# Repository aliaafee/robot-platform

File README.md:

# Robot Platform

An arduino based wheeled robot platform.

18650 battery holder

protection circuite
holder for two

2S 20A 7.4V w/Balance Lithium Li-ion 18650 Battery BMS Pack Protection PCB Board

LM2596 DC-DC Buck Converter Step Down Adjustable Power Supply Module

B0505S circuit isolator DC-DC converter

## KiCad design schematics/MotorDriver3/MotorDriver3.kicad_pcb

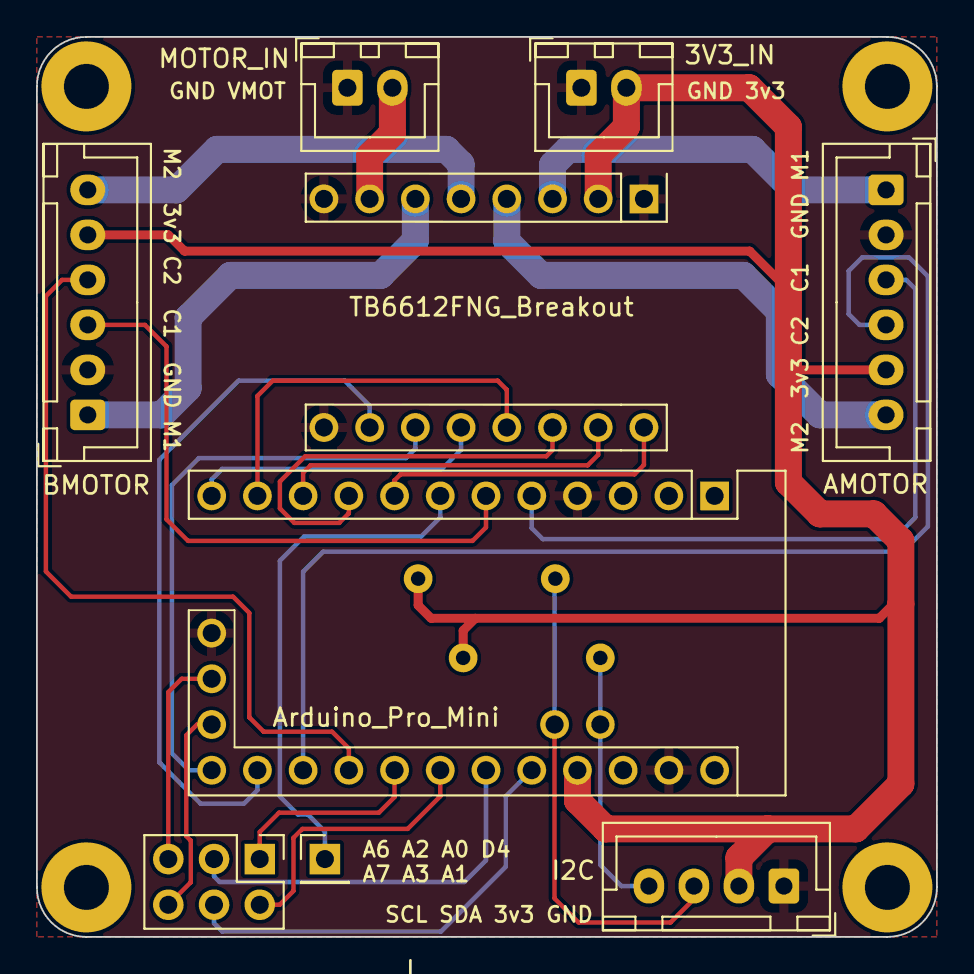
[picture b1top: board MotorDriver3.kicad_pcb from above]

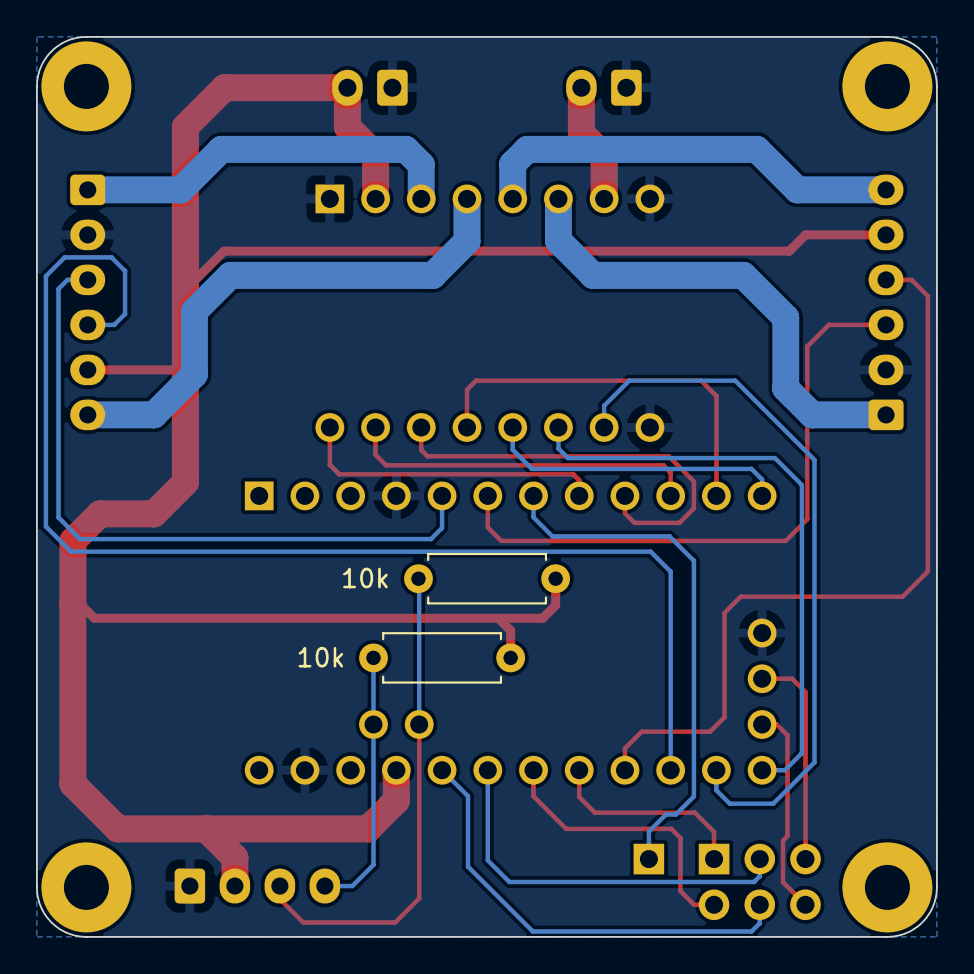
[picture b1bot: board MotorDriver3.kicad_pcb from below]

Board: 2 copper layers, 50.0 x 50.0 mm, 15 parts (2 on the bottom side), 27 nets.

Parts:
A2: Arduino_Pro_Mini; Arduino Pro Mini
H1, H2, H3, H4: MountingHole_Pad; MountingHole_2.5mm_Pad
J1: AMOTOR; JST_XH_B6B-XH-A_1x06_P2.50mm_Vertical
J2: BMOTOR; JST_XH_B6B-XH-A_1x06_P2.50mm_Vertical
J3: I2C; JST_XH_B4B-XH-A_1x04_P2.50mm_Vertical
J4: AnalogPins; PinHeader_2x03_P2.54mm_Vertical
J5: MOTOR_IN; JST_XH_B2B-XH-A_1x02_P2.50mm_Vertical
J6: 3V3_IN; JST_XH_B2B-XH-A_1x02_P2.50mm_Vertical
J7: Digital Pins; PinHeader_1x01_P2.54mm_Vertical
R1, R2: 10k; R_Axial_DIN0207_L6.3mm_D2.5mm_P7.62mm_Horizontal
U1: TB6612FNG_Breakout; TB6612FBG_Breakout

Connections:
+3V3: A2.26 (VCC), J1.5, J2.5, J3.2, J6.2, R1.1, R2.1, U1.2 (VCC)
A0: A2.20 (A0), J4.1
A1: A2.21 (A1), J4.2
A2: A2.22 (A2), J4.3
A3: A2.23 (A3), J4.4
A6: A2.14 (A6), J4.5
A7: A2.15 (A7), J4.6
AIN1: A2.10 (D7), U1.15 (AIN2)
AIN2: A2.9 (D6), U1.14 (AIN1)
AINT1: A2.5 (D2), J1.3
AINT2: A2.18 (D12), J1.4
AO1: J1.1, U1.3 (AO1)
AO2: J1.6, U1.4 (AO2)
BIN1: A2.12 (D9), U1.12 (BIN1)
BIN2: A2.16 (D10), U1.11 (BIN2)
BINT1: A2.6 (D3), J2.3
BINT2: A2.19 (D13), J2.4
BO1: J2.1, U1.6 (BO1)
BO2: J2.6, U1.5 (BO2)
D4: A2.7 (D4), J7.1
GND: A2.4 (GND), A2.13 (GND), A2.28 (GND), J1.2, J2.2, J3.1, J5.1, J6.1, U1.1 (GND), U1.8 (GND), U1.9 (GND)
PWMA: A2.8 (D5), U1.16 (PWMA)
PWMB: A2.17 (D11), U1.10 (PWMB)
SCL: A2.25 (A5), J3.4, R1.2
SDA: A2.24 (A4), J3.3, R2.2
STBY: A2.11 (D8), U1.13 (STBY)
VMOT: J5.2, U1.7 (VMOT)

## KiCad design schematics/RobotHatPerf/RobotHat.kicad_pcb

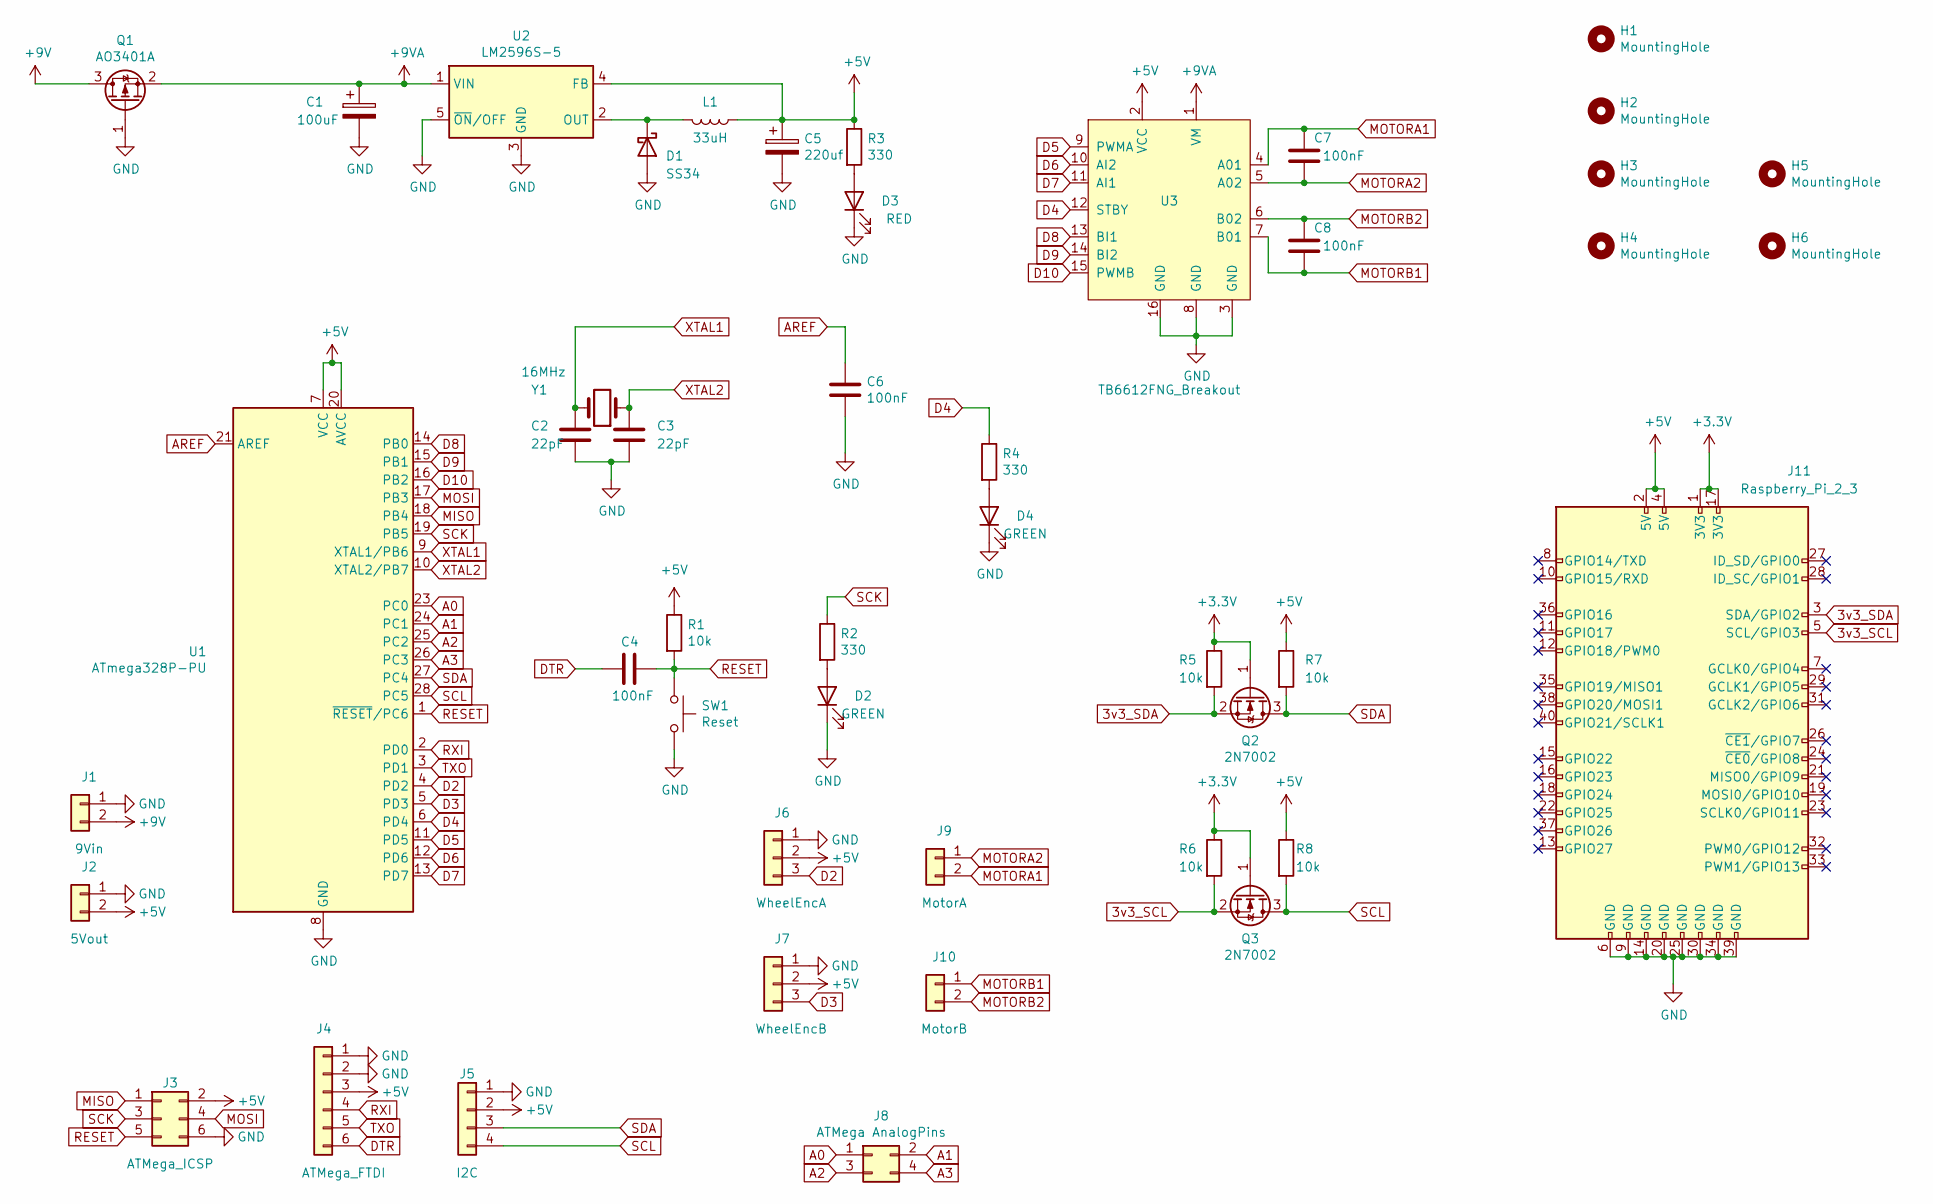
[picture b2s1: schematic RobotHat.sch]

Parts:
C1: 100uF; CP_Elec_6.3x7.7; Part C127971
C2, C3: 22pF; C_1206_3216Metric; Part C12891
C4, C6: 100nF; C_0402_1005Metric; Part C307331
C5: 220uf; CP_Elec_6.3x7.7; Part C371974
C7, C8: 100nF; C_1206_3216Metric; Part C24497
D1: SS34; Part C8678
D2, D4: GREEN; D_0402_1005Metric; Part C130719
D3: RED; D_0402_1005Metric; Part C130719
H1, H2, H3, H4, H5, H6: MountingHole; MountingHole_2.7mm_M2.5_DIN965_Pad
J1: 9Vin; JST_XH_B2B-XH-A_1x02_P2.50mm_Vertical
J2: 5Vout; JST_XH_B2B-XH-A_1x02_P2.50mm_Vertical
J3: ATMega_ICSP; PinHeader_2x03_P2.54mm_Vertical
J4: ATMega_FTDI; PinHeader_1x06_P2.54mm_Horizontal
J5: I2C; JST_XH_B4B-XH-A_1x04_P2.50mm_Vertical
J6: WheelEncA; JST_XH_B3B-XH-A_1x03_P2.50mm_Vertical
J7: WheelEncB; JST_XH_B3B-XH-A_1x03_P2.50mm_Vertical
J8: ATMega AnalogPins; PinSocket_1x04_P2.54mm_Horizontal
J9: MotorA; JST_XH_B2B-XH-A_1x02_P2.50mm_Vertical
J10: MotorB; JST_XH_B2B-XH-A_1x02_P2.50mm_Vertical
J11: Raspberry_Pi_2_3; PinSocket_2x20_P2.54mm_Vertical
L1: 33uH; YPRH1207-330M; Part C339951
Q1: AO3401A; SOT-23; Part C15127
Q2, Q3: 2N7002; SOT-23; Part C8545
R1, R5, R6, R7, R8: 10k; R_0805_2012Metric; Part C17724
R2, R3, R4: 330; R_0402_1005Metric; Part C25741
SW1: Reset; TS-1187A-B-A-B_PushButton; Part C318884
U1: ATmega328P-PU; DIP-28_W7.62mm
U2: LM2596S-5; TO-263-5_TabPin3; Part C194349
U3: TB6612FNG_Breakout
Y1: 16MHz; Crystal_HC49-U_Vertical

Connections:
3v3_SCL: J11.5 (SCL/GPIO3), Q3.2 (S), R6.2
3v3_SDA: J11.3 (SDA/GPIO2), Q2.2 (S), R5.2
+3V3: J11.1 (3V3), J11.17 (3V3), Q2.1 (G), Q3.1 (G), R5.1, R6.1
+5V: C5.1, J2.2, J3.2, J4.3, J5.2, J6.2, J7.2, J11.2 (5V), J11.4 (5V), L1.1, R1.1, R3.1, R7.1, R8.1, U1.7 (VCC), U1.20 (AVCC), U2.4 (FB), U3.2 (VCC)
+9V: J1.2, Q1.3 (D)
+9VA: C1.1, Q1.2 (S), U2.1 (VIN), U3.1 (VM)
A0: J8.1, U1.23 (PC0)
A1: J8.2, U1.24 (PC1)
A2: J8.3, U1.25 (PC2)
A3: J8.4, U1.26 (PC3)
AREF: C6.2, U1.21 (AREF)
D2: J6.3, U1.4 (PD2)
D3: J7.3, U1.5 (PD3)
D4: R4.1, U1.6 (PD4), U3.12 (STBY)
D5: U1.11 (PD5), U3.9 (PWMA)
D6: U1.12 (PD6), U3.10 (AI2)
D7: U1.13 (PD7), U3.11 (AI1)
D8: U1.14 (PB0), U3.13 (BI1)
D9: U1.15 (PB1), U3.14 (BI2)
D10: U1.16 (PB2), U3.15 (PWMB)
DTR: C4.1, J4.6
GND: C1.2, C2.2, C3.2, C5.2, C6.1, D1.2 (A), D2.1 (K), D3.1 (K), D4.1 (K), J1.1, J2.1, J3.6, J4.1, J4.2, J5.1, J6.1, J7.1, J11.6 (GND), J11.9 (GND), J11.14 (GND), J11.20 (GND), J11.25 (GND), J11.30 (GND), J11.34 (GND), J11.39 (GND), Q1.1 (G), SW1.2, U1.8 (GND), U1.22 (GND), U2.3 (GND), U2.5 (~ON~/OFF), U3.3 (GND), U3.8 (GND), U3.16 (GND)
MISO: J3.1, U1.18 (PB4)
MOSI: J3.4, U1.17 (PB3)
MOTORA1: C7.1, J9.2, U3.4 (A01)
MOTORA2: C7.2, J9.1, U3.5 (A02)
MOTORB1: C8.2, J10.1, U3.7 (B01)
MOTORB2: C8.1, J10.2, U3.6 (B02)
unnamed: D1.1 (K), L1.2, U2.2 (OUT)
unnamed: D2.2 (A), R2.2
unnamed: D3.2 (A), R3.2
unnamed: D4.2 (A), R4.2
RESET: C4.2, J3.5, R1.2, SW1.1, U1.1 (~RESET~/PC6)
RXI: J4.4, U1.2 (PD0)
SCK: J3.3, R2.1, U1.19 (PB5)
SCL: J5.4, Q3.3 (D), R8.2, U1.28 (PC5)
SDA: J5.3, Q2.3 (D), R7.2, U1.27 (PC4)
TXO: J4.5, U1.3 (PD1)
XTAL1: C2.1, U1.9 (XTAL1/PB6), Y1.2
XTAL2: C3.1, U1.10 (XTAL2/PB7), Y1.1

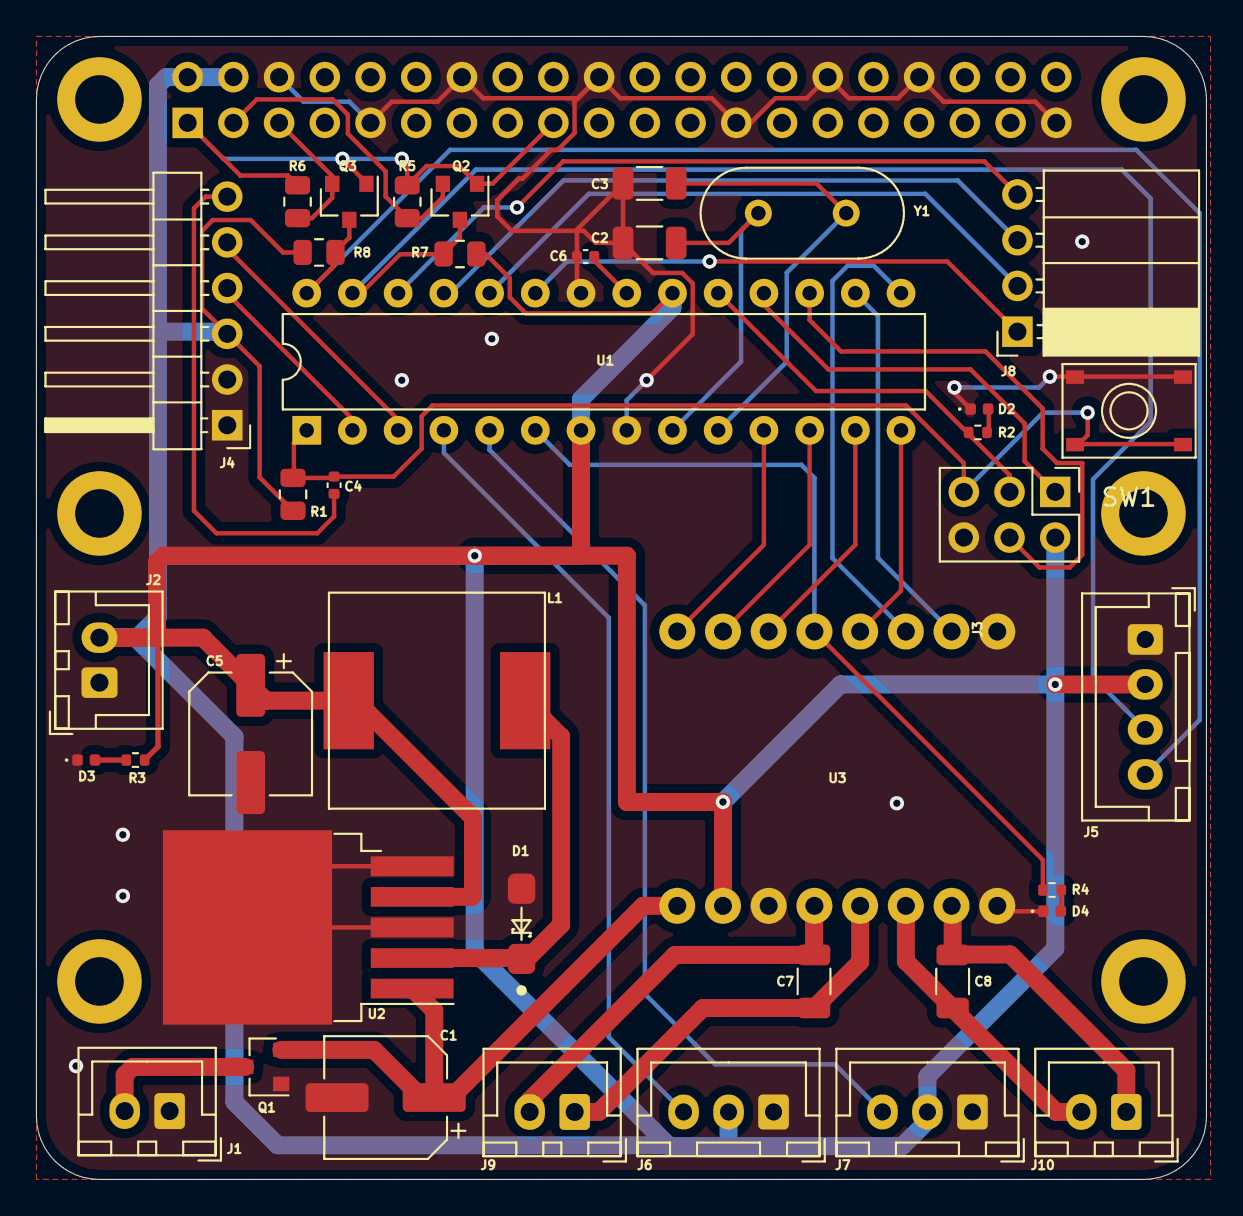
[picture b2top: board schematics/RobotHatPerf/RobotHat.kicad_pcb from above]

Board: 2 copper layers, 65.0 x 63.5 mm, 46 parts (1 on the bottom side), 40 nets.

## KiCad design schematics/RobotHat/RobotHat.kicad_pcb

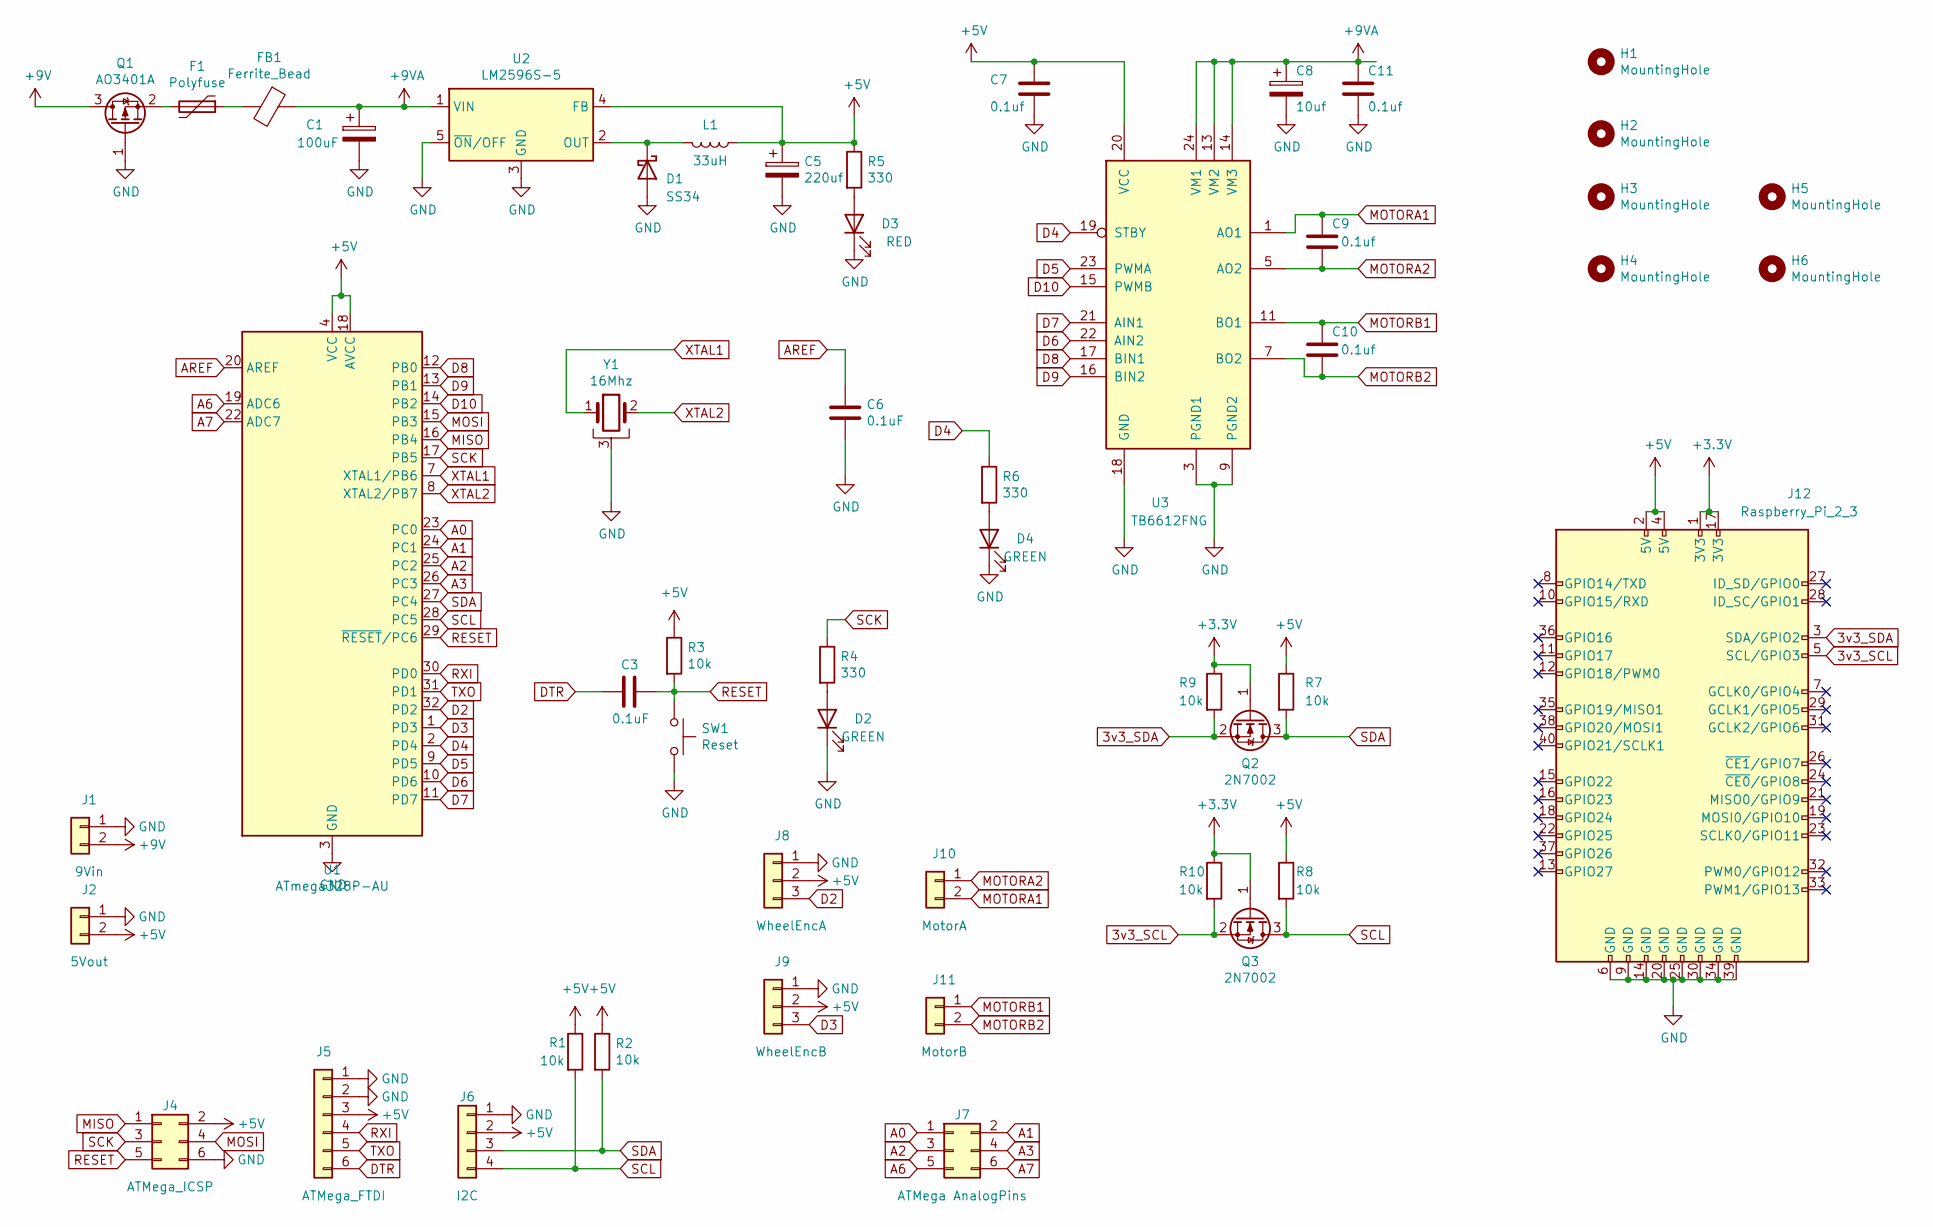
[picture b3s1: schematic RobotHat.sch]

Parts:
C1: 100uF; CP_Radial_D5.0mm_P2.50mm
C3, C6: 0.1uF; C_0402_1005Metric
C5: 220uf; CP_Radial_D5.0mm_P2.50mm
C7, C9, C10, C11: 0.1uf; C_1206_3216Metric
C8: 10uf; CP_Radial_D4.0mm_P2.00mm
D1: SS34
D2, D4: GREEN; D_0402_1005Metric
D3: RED; D_0402_1005Metric
F1: Polyfuse; Fuse_1206_3216Metric
FB1: Ferrite_Bead; L_0805_2012Metric
H1, H2, H3, H4, H5, H6: MountingHole; MountingHole_2.7mm_M2.5_DIN965_Pad
J1: 9Vin; JST_XH_B2B-XH-A_1x02_P2.50mm_Vertical
J2: 5Vout; JST_XH_B2B-XH-A_1x02_P2.50mm_Vertical
J4: ATMega_ICSP; PinHeader_2x03_P2.54mm_Vertical
J5: ATMega_FTDI; PinHeader_1x06_P2.54mm_Horizontal
J6: I2C; JST_GH_BM04B-GHS-TBT_1x04-1MP_P1.25mm_Vertical
J7: ATMega AnalogPins; PinSocket_2x03_P2.54mm_Horizontal
J8: WheelEncA; JST_XH_B3B-XH-A_1x03_P2.50mm_Vertical
J9: WheelEncB; JST_XH_B3B-XH-A_1x03_P2.50mm_Vertical
J10: MotorA; JST_XH_B2B-XH-A_1x02_P2.50mm_Vertical
J11: MotorB; JST_XH_B2B-XH-A_1x02_P2.50mm_Vertical
J12: Raspberry_Pi_2_3; PinSocket_2x20_P2.54mm_Vertical
L1: 33uH; YPRH1207-330M; Part No C339951
Q1: AO3401A; SOT-23
Q2, Q3: 2N7002; SOT-23
R1, R2: 10k; R_1206_3216Metric
R3, R7, R8, R9, R10: 10k; R_0402_1005Metric
R4, R5, R6: 330; R_0402_1005Metric
SW1: Reset; SW_Push_1P1T_NO_Vertical_Wuerth_434133025816
U1: ATmega328P-AU; TQFP-32_7x7mm_P0.8mm
U2: LM2596S-5; TO-263-5_TabPin3
U3: TB6612FNG; SSOP-24_5.3x8.2mm_P0.65mm
Y1: 16Mhz; CSTCE16M0V53-R0

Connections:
3v3_SCL: J12.5 (SCL/GPIO3), Q3.2 (S), R10.2
3v3_SDA: J12.3 (SDA/GPIO2), Q2.2 (S), R9.2
+3V3: J12.1 (3V3), J12.17 (3V3), Q2.1 (G), Q3.1 (G), R9.1, R10.1
+5V: C5.1, C7.1, J2.2, J4.2, J5.3, J6.2, J8.2, J9.2, J12.2 (5V), J12.4 (5V), L1.1, R1.1, R2.1, R3.1, R5.1, R7.1, R8.1, U1.4 (VCC), U1.6 (VCC), U1.18 (AVCC), U2.4 (FB), U3.20 (VCC)
+9V: J1.2, Q1.3 (D)
+9VA: C1.1, C8.1, C11.1, F1.2, FB1.1, Q1.2 (S), U2.1 (VIN), U3.13 (VM2), U3.14 (VM3), U3.24 (VM1)
A0: J7.1, U1.23 (PC0)
A1: J7.2, U1.24 (PC1)
A2: J7.3, U1.25 (PC2)
A3: J7.4, U1.26 (PC3)
A6: J7.5, U1.19 (ADC6)
A7: J7.6, U1.22 (ADC7)
AREF: C6.2, U1.20 (AREF)
D2: J8.3, U1.32 (PD2)
D3: J9.3, U1.1 (PD3)
D4: R6.1, U1.2 (PD4), U3.19 (STBY)
D5: U1.9 (PD5), U3.23 (PWMA)
D6: U1.10 (PD6), U3.22 (AIN2)
D7: U1.11 (PD7), U3.21 (AIN1)
D8: U1.12 (PB0), U3.17 (BIN1)
D9: U1.13 (PB1), U3.16 (BIN2)
D10: U1.14 (PB2), U3.15 (PWMB)
DTR: C3.1, J5.6
GND: C1.2, C5.2, C6.1, C7.2, C8.2, C11.2, D1.2 (A), D2.1 (K), D3.1 (K), D4.1 (K), J1.1, J2.1, J4.6, J5.1, J5.2, J6.1, J8.1, J9.1, J12.6 (GND), J12.9 (GND), J12.14 (GND), J12.20 (GND), J12.25 (GND), J12.30 (GND), J12.34 (GND), J12.39 (GND), Q1.1 (G), SW1.2, U1.3 (GND), U1.5 (GND), U1.21 (GND), U2.3 (GND), U2.5 (~ON~/OFF), U3.3 (PGND1), U3.4 (PGND1), U3.9 (PGND2), U3.10 (PGND2), U3.18 (GND), Y1.3
MISO: J4.1, U1.16 (PB4)
MOSI: J4.4, U1.15 (PB3)
MOTORA1: C9.1, J10.2, U3.1 (AO1), U3.2 (AO1)
MOTORA2: C9.2, J10.1, U3.5 (AO2), U3.6 (AO2)
MOTORB1: C10.1, J11.1, U3.11 (BO1), U3.12 (BO1)
MOTORB2: C10.2, J11.2, U3.7 (BO2), U3.8 (BO2)
unnamed: D1.1 (K), L1.2, U2.2 (OUT)
unnamed: D2.2 (A), R4.2
unnamed: D3.2 (A), R5.2
unnamed: D4.2 (A), R6.2
unnamed: F1.1, FB1.2
RESET: C3.2, J4.5, R3.2, SW1.1, U1.29 (~RESET~/PC6)
RXI: J5.4, U1.30 (PD0)
SCK: J4.3, R4.1, U1.17 (PB5)
SCL: J6.4, Q3.3 (D), R1.2, R8.2, U1.28 (PC5)
SDA: J6.3, Q2.3 (D), R2.2, R7.2, U1.27 (PC4)
TXO: J5.5, U1.31 (PD1)
XTAL1: U1.7 (XTAL1/PB6), Y1.1
XTAL2: U1.8 (XTAL2/PB7), Y1.2

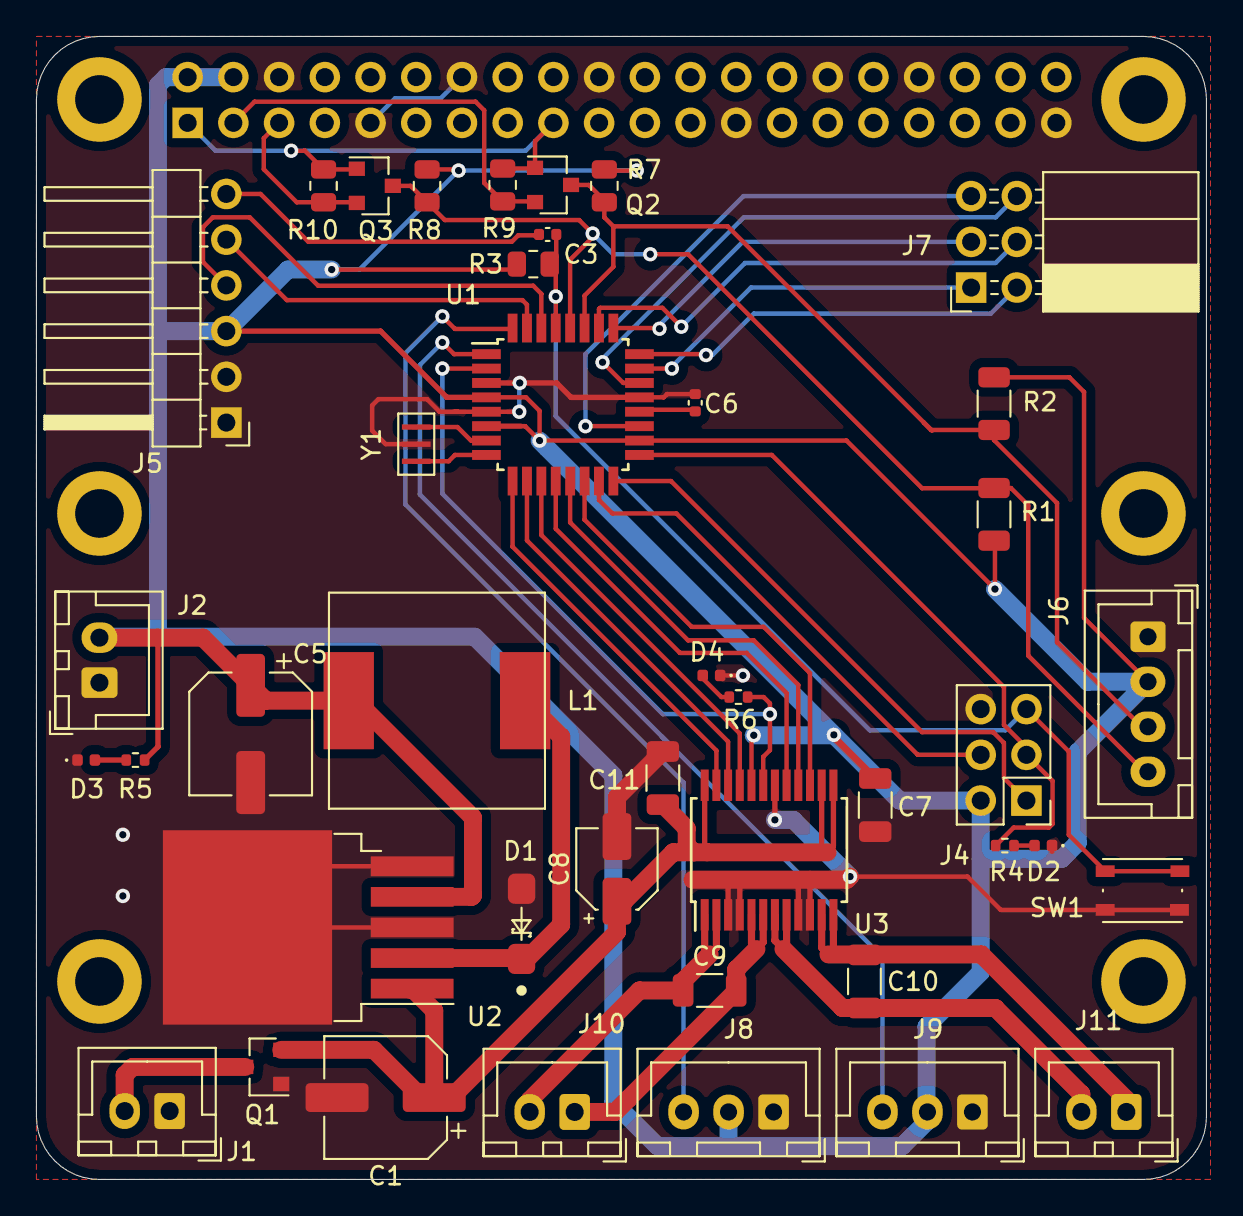
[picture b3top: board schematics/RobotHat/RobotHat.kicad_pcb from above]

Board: 2 copper layers, 65.0 x 63.5 mm, 49 parts (1 on the bottom side), 42 nets.

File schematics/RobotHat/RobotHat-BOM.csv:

Designator,Comment,Footprint,JLCPCB Part #
C1,100uF,Capacitor_SMD:CP_Elec_6.3x7.7,C127971
C3,100nF,Capacitor_SMD:C_0402_1005Metric,C307331
C5,220uf,Capacitor_SMD:CP_Elec_6.3x7.7,C371974
C6,100nF,Capacitor_SMD:C_0402_1005Metric,C307331
C7,100nF,Capacitor_SMD:C_1206_3216Metric,C307331
C8,10uf,Capacitor_SMD:CP_Elec_4x5.3,C134721
C9,100nF,Capacitor_SMD:C_1206_3216Metric,C307331
C10,100nF,Capacitor_SMD:C_1206_3216Metric,C307331
C11,100nF,Capacitor_SMD:C_1206_3216Metric,C307331
D1,SS34,RobotHat:SS34,C8678
D2,GREEN,Diode_SMD:D_0402_1005Metric,C130719
D3,RED,Diode_SMD:D_0402_1005Metric,C130719
D4,GREEN,Diode_SMD:D_0402_1005Metric,C130719
L1,33uH,RobotHat:YPRH1207-330M,C339951
Q1,AO3401A,Package_TO_SOT_SMD:SOT-23,C15127
Q2,2N7002,Package_TO_SOT_SMD:SOT-23,C8545
Q3,2N7002,Package_TO_SOT_SMD:SOT-23,C8545
R3,10k,Resistor_SMD:R_0805_2012Metric,C17724
R4,330,Resistor_SMD:R_0402_1005Metric,C25741
R5,330,Resistor_SMD:R_0402_1005Metric,C25741
R6,330,Resistor_SMD:R_0402_1005Metric,C25741
R7,10k,Resistor_SMD:R_0805_2012Metric,C17724
R8,10k,Resistor_SMD:R_0805_2012Metric,C17724
R9,10k,Resistor_SMD:R_0805_2012Metric,C17724
R10,10k,Resistor_SMD:R_0805_2012Metric,C17724
U1,ATmega328P-AU,Package_QFP:TQFP-32_7x7mm_P0.8mm,C14877
U2,LM2596S-5,Package_TO_SOT_SMD:TO-263-5_TabPin3,C194349
U3,TB6612FNG,Package_SO:SSOP-24_5.3x8.2mm_P0.65mm,C141517
Y1,16Mhz,RobotHat:CSTCE16M0V53-R0,C32180

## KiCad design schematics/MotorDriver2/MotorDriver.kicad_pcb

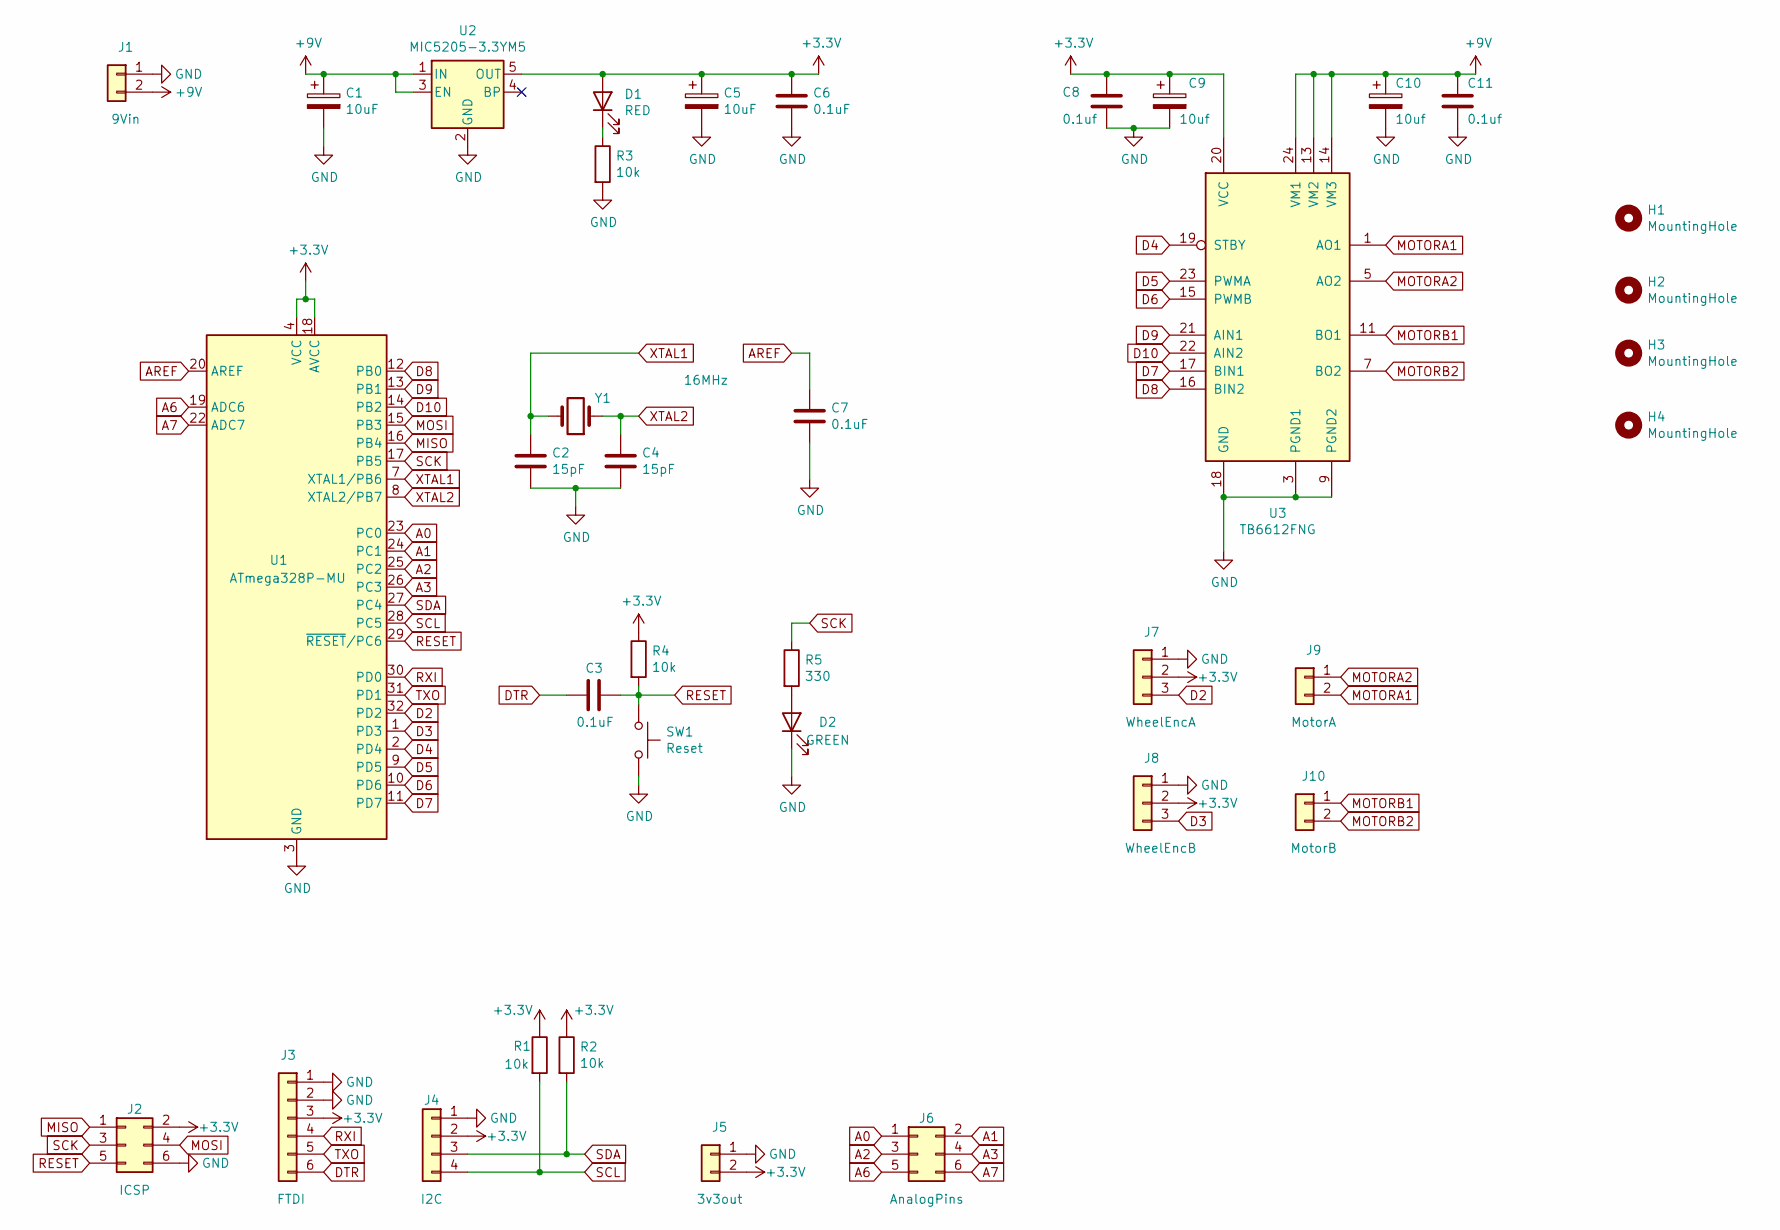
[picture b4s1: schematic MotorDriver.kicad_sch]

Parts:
C1, C5: 10uF; CP_Elec_4x5.4
C2, C4: 15pF; C_0402_1005Metric
C3, C6, C7: 0.1uF; C_0402_1005Metric
C8, C11: 0.1uf; C_0402_1005Metric
C9, C10: 10uf; CP_Elec_4x5.4
D1: RED; D_0402_1005Metric
D2: GREEN; D_0402_1005Metric
H1, H2, H3, H4: MountingHole; MountingHole_2.5mm
J1: 9Vin; JST_XH_B2B-XH-A_1x02_P2.50mm_Vertical
J2: ICSP; PinHeader_2x03_P2.54mm_Vertical
J3: FTDI; PinHeader_1x06_P2.54mm_Vertical
J4: I2C; JST_XH_B4B-XH-A_1x04_P2.50mm_Vertical
J5: 3v3out; JST_XH_B2B-XH-A_1x02_P2.50mm_Vertical
J6: AnalogPins; PinHeader_2x03_P2.54mm_Vertical
J7: WheelEncA; JST_XH_B3B-XH-A_1x03_P2.50mm_Vertical
J8: WheelEncB; JST_XH_B3B-XH-A_1x03_P2.50mm_Vertical
J9: MotorA; JST_XH_B2B-XH-A_1x02_P2.50mm_Vertical
J10: MotorB; JST_XH_B2B-XH-A_1x02_P2.50mm_Vertical
R1, R2, R3, R4: 10k; R_0402_1005Metric
R5: 330; R_0402_1005Metric
SW1: Reset; SW_SPST_B3U-1000P-B
U1: ATmega328P-MU; QFN-32-1EP_5x5mm_P0.5mm_EP3.1x3.1mm
U2: MIC5205-3.3YM5; SOT-23-5
U3: TB6612FNG; SSOP-24_5.3x8.2mm_P0.65mm
Y1: 16MHz; Crystal_SMD_HC49-SD

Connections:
+3V3: C5.1, C6.1, C8.1, C9.1, D1.2 (A), J2.2, J3.3, J4.2, J5.2, J7.2, J8.2, R1.1, R2.1, R4.1, U1.4 (VCC), U1.6 (VCC), U1.18 (AVCC), U2.5 (OUT), U3.20 (VCC)
+9V: C1.1, C10.1, C11.1, J1.2, U2.1 (IN), U2.3 (EN), U3.13 (VM2), U3.14 (VM3), U3.24 (VM1)
A0: J6.1, U1.23 (PC0)
A1: J6.2, U1.24 (PC1)
A2: J6.3, U1.25 (PC2)
A3: J6.4, U1.26 (PC3)
A6: J6.5, U1.19 (ADC6)
A7: J6.6, U1.22 (ADC7)
AREF: C7.2, U1.20 (AREF)
D2: J7.3, U1.32 (PD2)
D3: J8.3, U1.1 (PD3)
D4: U1.2 (PD4), U3.19 (STBY)
D5: U1.9 (PD5), U3.23 (PWMA)
D6: U1.10 (PD6), U3.15 (PWMB)
D7: U1.11 (PD7), U3.17 (BIN1)
D8: U1.12 (PB0), U3.16 (BIN2)
D9: U1.13 (PB1), U3.21 (AIN1)
D10: U1.14 (PB2), U3.22 (AIN2)
DTR: C3.1, J3.6
GND: C1.2, C2.1, C4.1, C5.2, C6.2, C7.1, C8.2, C9.2, C10.2, C11.2, D2.1 (K), J1.1, J2.6, J3.1, J3.2, J4.1, J5.1, J7.1, J8.1, R3.2, SW1.2, U1.3 (GND), U1.5 (GND), U1.21 (GND), U1.33 (GND), U2.2 (GND), U3.3 (PGND1), U3.4 (PGND1), U3.9 (PGND2), U3.10 (PGND2), U3.18 (GND)
MISO: J2.1, U1.16 (PB4)
MOSI: J2.4, U1.15 (PB3)
MOTORA1: J9.2, U3.1 (AO1), U3.2 (AO1)
MOTORA2: J9.1, U3.5 (AO2), U3.6 (AO2)
MOTORB1: J10.1, U3.11 (BO1), U3.12 (BO1)
MOTORB2: J10.2, U3.7 (BO2), U3.8 (BO2)
unnamed: D1.1 (K), R3.1
unnamed: D2.2 (A), R5.2
RESET: C3.2, J2.5, R4.2, SW1.1, U1.29 (~RESET/PC6)
RXI: J3.4, U1.30 (PD0)
SCK: J2.3, R5.1, U1.17 (PB5)
SCL: J4.4, R1.2, U1.28 (PC5)
SDA: J4.3, R2.2, U1.27 (PC4)
TXO: J3.5, U1.31 (PD1)
XTAL1: C2.2, U1.7 (XTAL1/PB6), Y1.2
XTAL2: C4.2, U1.8 (XTAL2/PB7), Y1.1

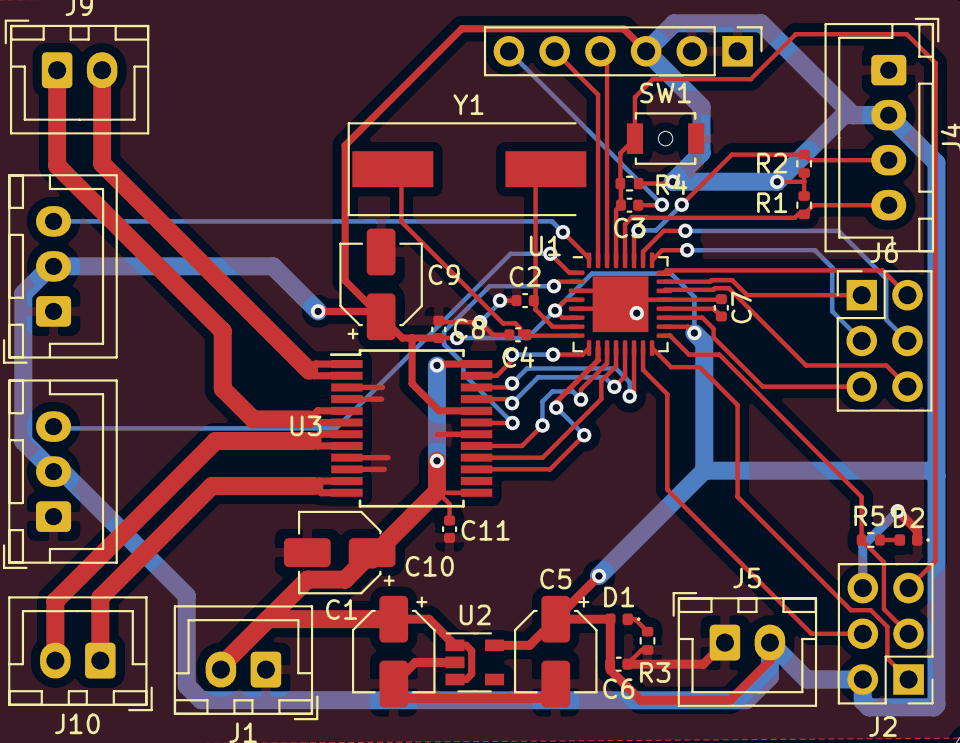
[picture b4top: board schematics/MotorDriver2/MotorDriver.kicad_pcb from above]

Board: 2 copper layers, 37 parts (0 on the bottom side), 36 nets.
